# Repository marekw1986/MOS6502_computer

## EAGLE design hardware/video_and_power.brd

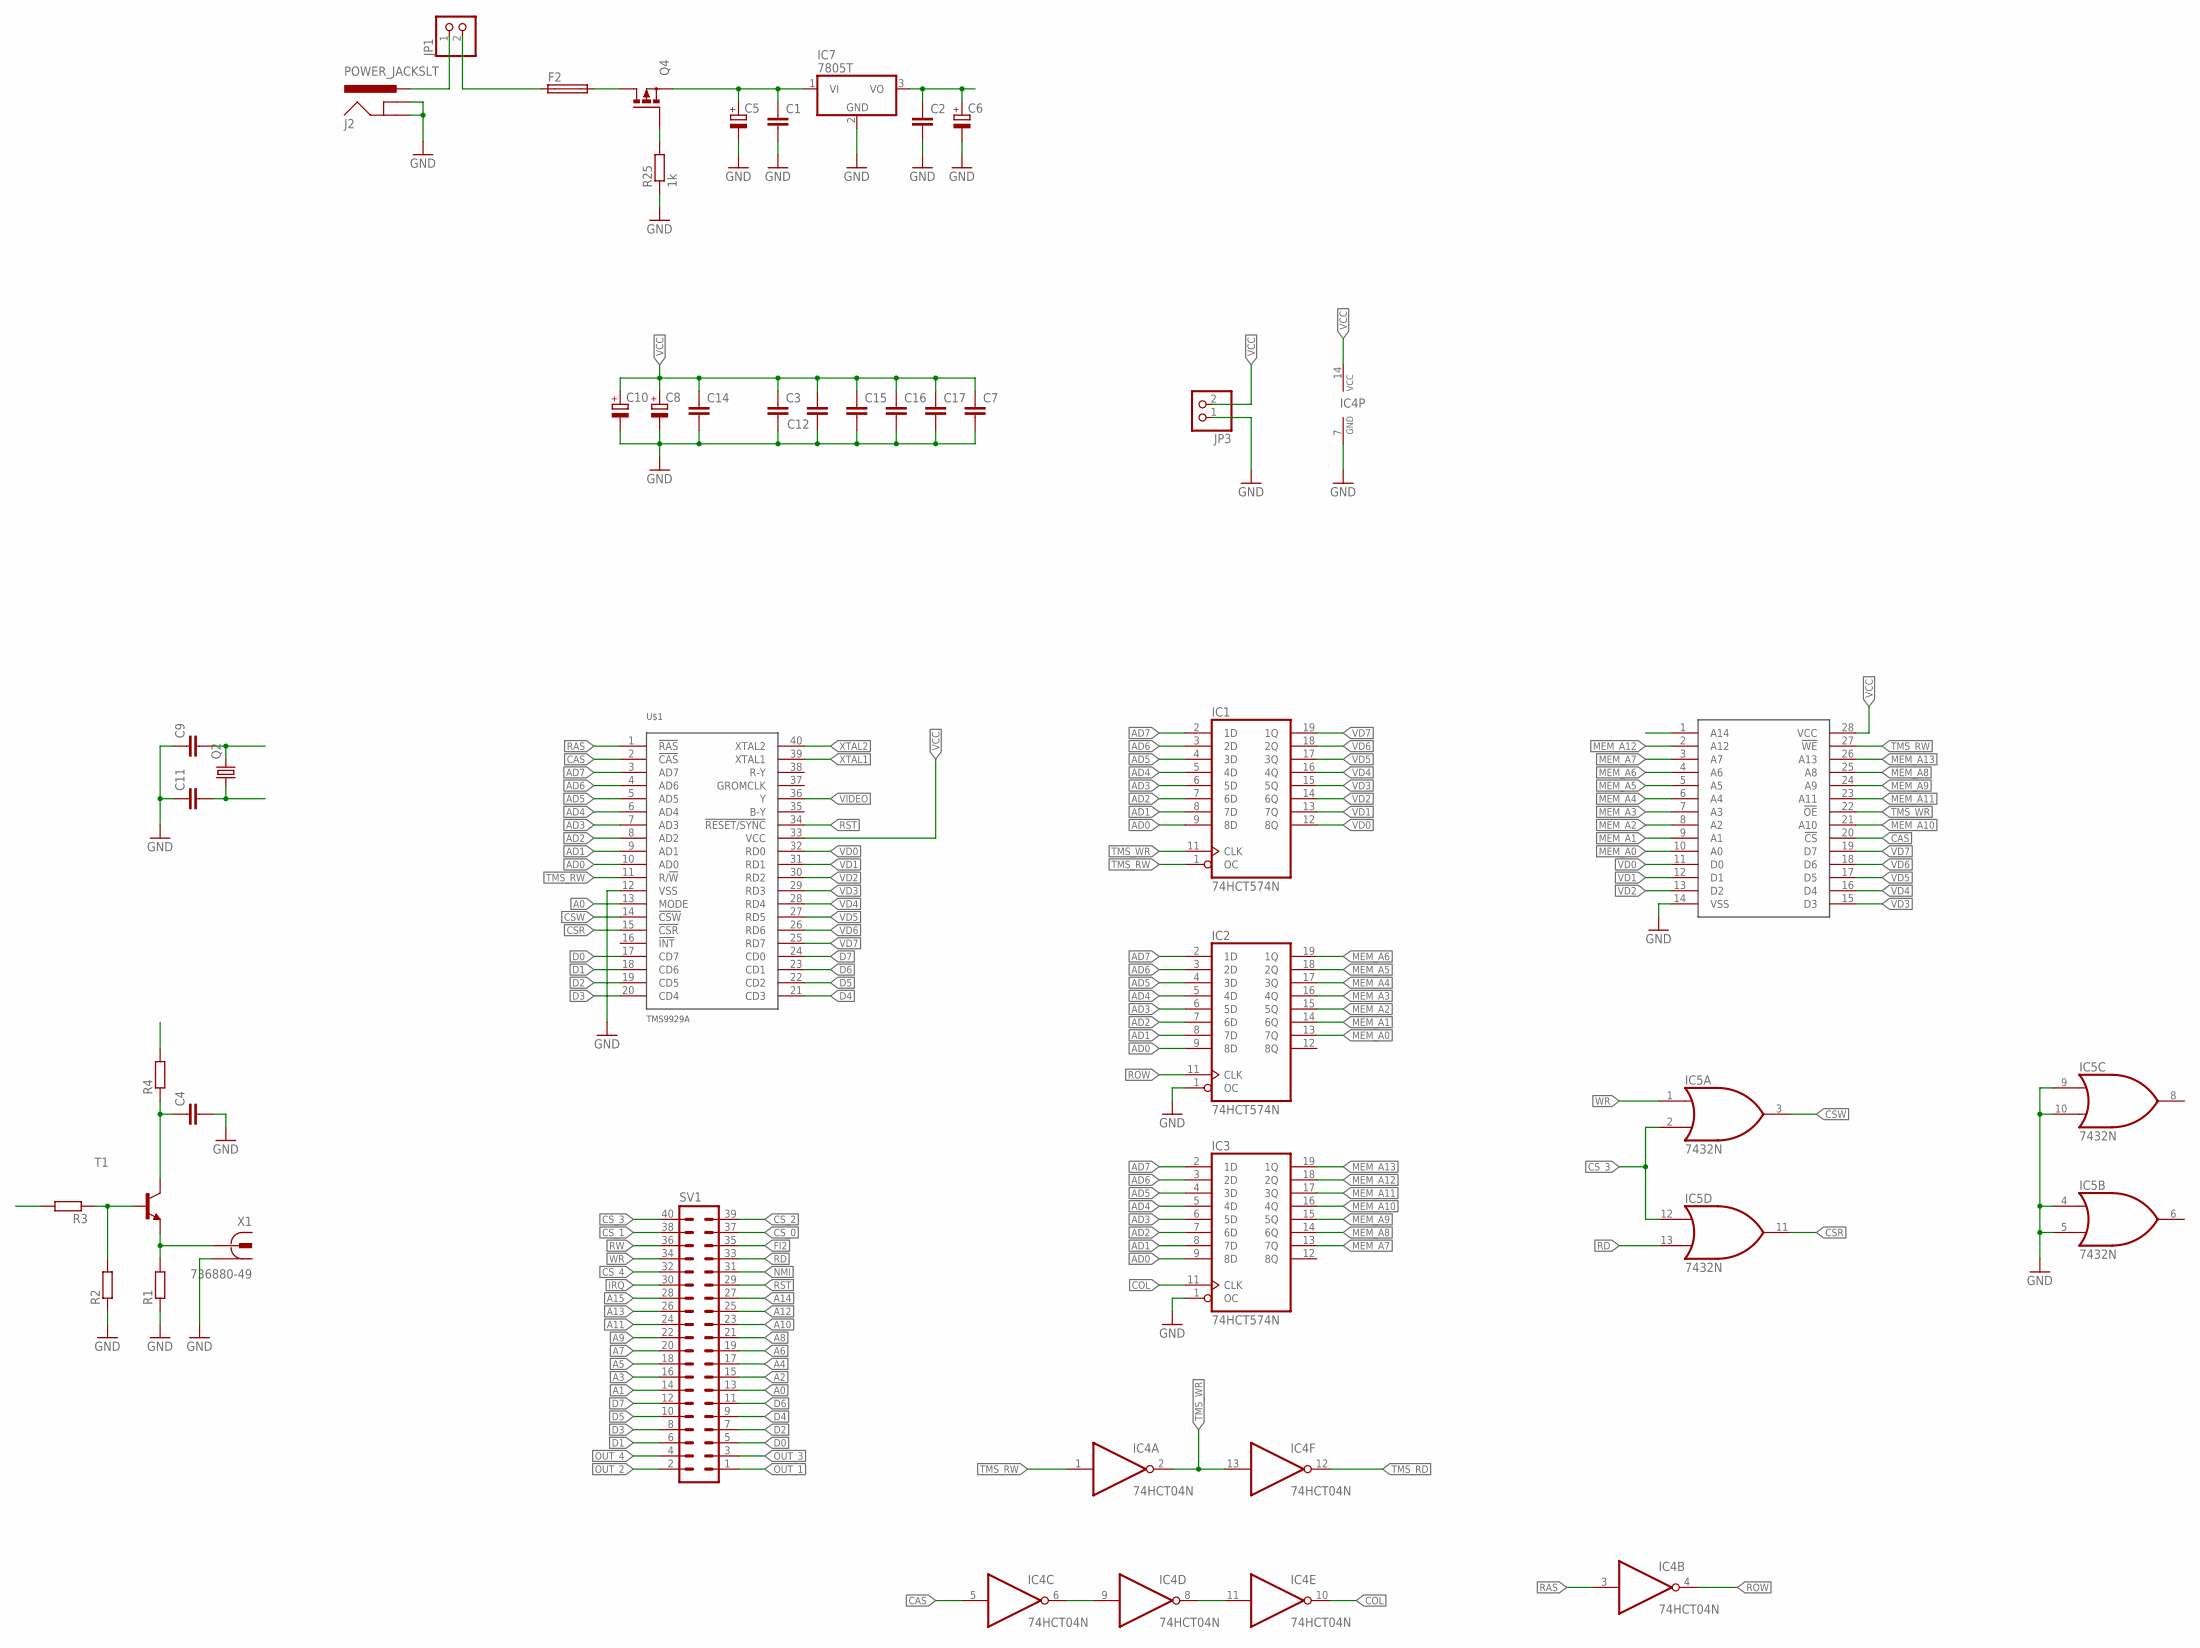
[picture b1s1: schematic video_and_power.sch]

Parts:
C1, C2, C7, C14, C15: C-EUC1206; C1206
C3, C4, C9, C11, C12, C16, C17: C-EUC0603; C0603
C5, C6, C8, C10: CPOL-EUE5-10.5; E5-10,5
F2: SH22,5; MPN 0031.8201
IC1, IC2, IC3: 74HCT574N; DIL20
IC4: 74HCT04N; DIL14
IC5: 7432N; DIL14
IC7: 7805T; TO220H
J2: POWER_JACKSLT; POWER_JACK_SLOT
JP1: PINHD-1X2; 1X02
JP3: PINHD-1X2/90; 1X02/90
Q2: CRYSTALHC49S; HC49/S
Q4: P-MOSFET-SO8; SO-08
R1, R2: R-EU_R0603; R0603
R3: R-EU_0204/7; 0204/7
R4: R-EU_R0805; R0805
R25: 1k; R0603
SV1: ML40L
T1: 2N4401-NPN-TO92-EBC; TO92-EBC
U$1: TMS9929A; DIL40
U$2: 62256; DIL28-6
X1: 736880-49

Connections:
9V: C1.1, C5.+, IC7.1 (VI), Q4.1 (S), Q4.2 (S), Q4.3 (S)
A0: SV1.13, U$1.13 (MODE)
A1: SV1.14
A2: SV1.15
A3: SV1.16
A4: SV1.17
A5: SV1.18
A6: SV1.19
A7: SV1.20
A8: SV1.21
A9: SV1.22
A10: SV1.23
A11: SV1.24
A12: SV1.25
A13: SV1.26
A14: SV1.27
A15: SV1.28
AD0: IC1.9 (8D), IC2.9 (8D), IC3.9 (8D), U$1.10 (AD0)
AD1: IC1.8 (7D), IC2.8 (7D), IC3.8 (7D), U$1.9 (AD1)
AD2: IC1.7 (6D), IC2.7 (6D), IC3.7 (6D), U$1.8 (AD2)
AD3: IC1.6 (5D), IC2.6 (5D), IC3.6 (5D), U$1.7 (AD3)
AD4: IC1.5 (4D), IC2.5 (4D), IC3.5 (4D), U$1.6 (AD4)
AD5: IC1.4 (3D), IC2.4 (3D), IC3.4 (3D), U$1.5 (AD5)
AD6: IC1.3 (2D), IC2.3 (2D), IC3.3 (2D), U$1.4 (AD6)
AD7: IC1.2 (1D), IC2.2 (1D), IC3.2 (1D), U$1.3 (AD7)
CAS: IC4.5 (I), U$1.2 (!CAS), U$2.20 (!CS)
COL: IC3.11 (CLK), IC4.10 (O)
CSR: IC5.11 (O), U$1.15 (!CSR)
CSW: IC5.3 (O), U$1.14 (!CSW)
CS_0: SV1.37
CS_1: SV1.38
CS_2: SV1.39
CS_3: IC5.2 (I1), IC5.12 (I0), SV1.40
CS_4: SV1.32
D0: SV1.5, U$1.17 (CD7)
D1: SV1.6, U$1.18 (CD6)
D2: SV1.7, U$1.19 (CD5)
D3: SV1.8, U$1.20 (CD4)
D4: SV1.9, U$1.21 (CD3)
D5: SV1.10, U$1.22 (CD2)
D6: SV1.11, U$1.23 (CD1)
D7: SV1.12, U$1.24 (CD0)
FI2: SV1.35
GND: C1.2, C2.2, C3.2, C4.2, C5.-, C6.-, C7.2, C8.-, C9.1, C10.-, C11.1, C12.1, C14.2, C15.2, C16.2, C17.2, IC1.10 (GND), IC2.1 (OC), IC2.10 (GND), IC3.1 (OC), IC3.10 (GND), IC4.7 (GND), IC5.4 (I0), IC5.5 (I1), IC5.7 (GND), IC5.9 (I0), IC5.10 (I1), IC7.2 (GND), J2.GND@1 (GNDBREAK), J2.GND@2 (GND), JP3.1, R1.1, R2.1, R25.1, U$1.12 (VSS), U$2.14 (VSS), X1.1, X1.1@1 (1), X1.1@2 (1)
IRQ: SV1.30
MEM_A0: IC2.13 (7Q), U$2.10 (A0)
MEM_A1: IC2.14 (6Q), U$2.9 (A1)
MEM_A2: IC2.15 (5Q), U$2.8 (A2)
MEM_A3: IC2.16 (4Q), U$2.7 (A3)
MEM_A4: IC2.17 (3Q), U$2.6 (A4)
MEM_A5: IC2.18 (2Q), U$2.5 (A5)
MEM_A6: IC2.19 (1Q), U$2.4 (A6)
MEM_A7: IC3.13 (7Q), U$2.3 (A7)
MEM_A8: IC3.14 (6Q), U$2.25 (A8)
MEM_A9: IC3.15 (5Q), U$2.24 (A9)
MEM_A10: IC3.16 (4Q), U$2.21 (A10)
MEM_A11: IC3.17 (3Q), U$2.23 (A11)
MEM_A12: IC3.18 (2Q), U$2.2 (A12)
MEM_A13: IC3.19 (1Q), U$2.26 (A13)
unnamed: IC4.6 (O), IC4.9 (I)
unnamed: IC4.8 (O), IC4.11 (I)
unnamed: Q4.4 (G), R25.2
unnamed: J2.PWR, JP1.1
unnamed: R1.2, T1.E, X1.2
unnamed: R2.2, R3.1, T1.B
unnamed: C4.1, R4.1, T1.C
unnamed: F2.1, JP1.2
unnamed: F2.2, Q4.5 (D), Q4.6 (D), Q4.7 (D), Q4.8 (D)
NMI: SV1.31
OUT_1: SV1.1
OUT_2: SV1.2
OUT_3: SV1.3, U$2.1 (A14)
OUT_4: SV1.4
RAS: IC4.3 (I), U$1.1 (!RAS)
RD: IC5.13 (I1), SV1.33
ROW: IC2.11 (CLK), IC4.4 (O)
RST: SV1.29, U$1.34 (!RESET/SYNC)
RW: SV1.36
TMS_RD: IC4.12 (O)
TMS_RW: IC1.1 (OC), IC4.1 (I), U$1.11 (R/!W), U$2.27 (!WE)
TMS_WR: IC1.11 (CLK), IC4.2 (O), IC4.13 (I), U$2.22 (!OE)
VCC: C2.1, C3.1, C6.+, C7.1, C8.+, C10.+, C12.2, C14.1, C15.1, C16.1, C17.1, IC1.20 (VCC), IC2.20 (VCC), IC3.20 (VCC), IC4.14 (VCC), IC5.14 (VCC), IC7.3 (VO), JP3.2, R4.2, U$1.33 (VCC), U$2.28 (VCC)
VD0: IC1.12 (8Q), U$1.32 (RD0), U$2.11 (D0)
VD1: IC1.13 (7Q), U$1.31 (RD1), U$2.12 (D1)
VD2: IC1.14 (6Q), U$1.30 (RD2), U$2.13 (D2)
VD3: IC1.15 (5Q), U$1.29 (RD3), U$2.15 (D3)
VD4: IC1.16 (4Q), U$1.28 (RD4), U$2.16 (D4)
VD5: IC1.17 (3Q), U$1.27 (RD5), U$2.17 (D5)
VD6: IC1.18 (2Q), U$1.26 (RD6), U$2.18 (D6)
VD7: IC1.19 (1Q), U$1.25 (RD7), U$2.19 (D7)
VIDEO: R3.2, U$1.36 (Y)
WR: IC5.1 (I0), SV1.34
XTAL1: C9.2, Q2.2, U$1.39 (XTAL1)
XTAL2: C11.2, Q2.1, U$1.40 (XTAL2)

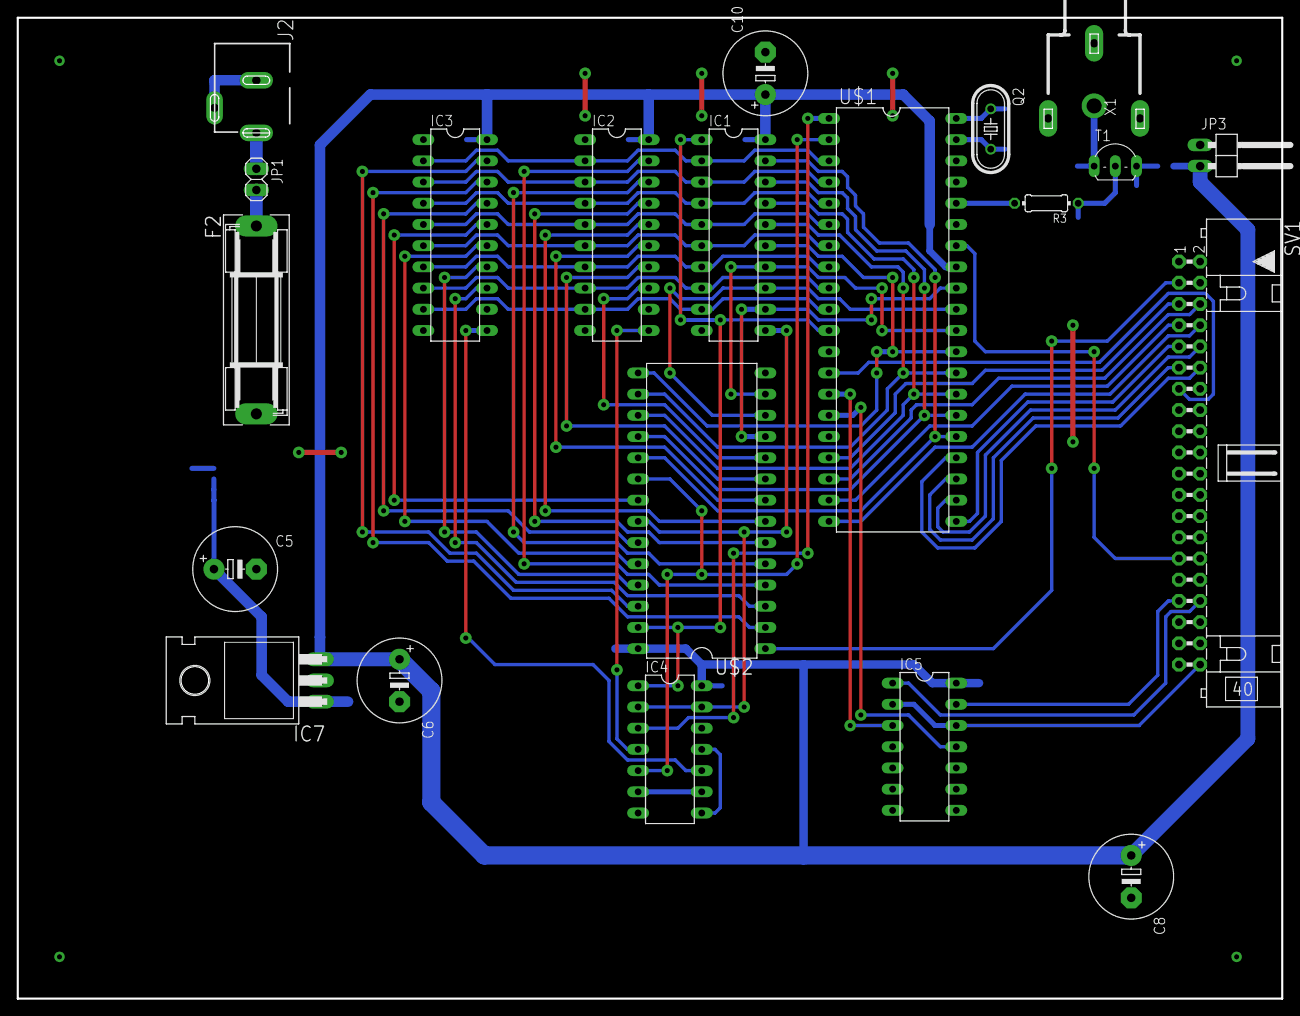
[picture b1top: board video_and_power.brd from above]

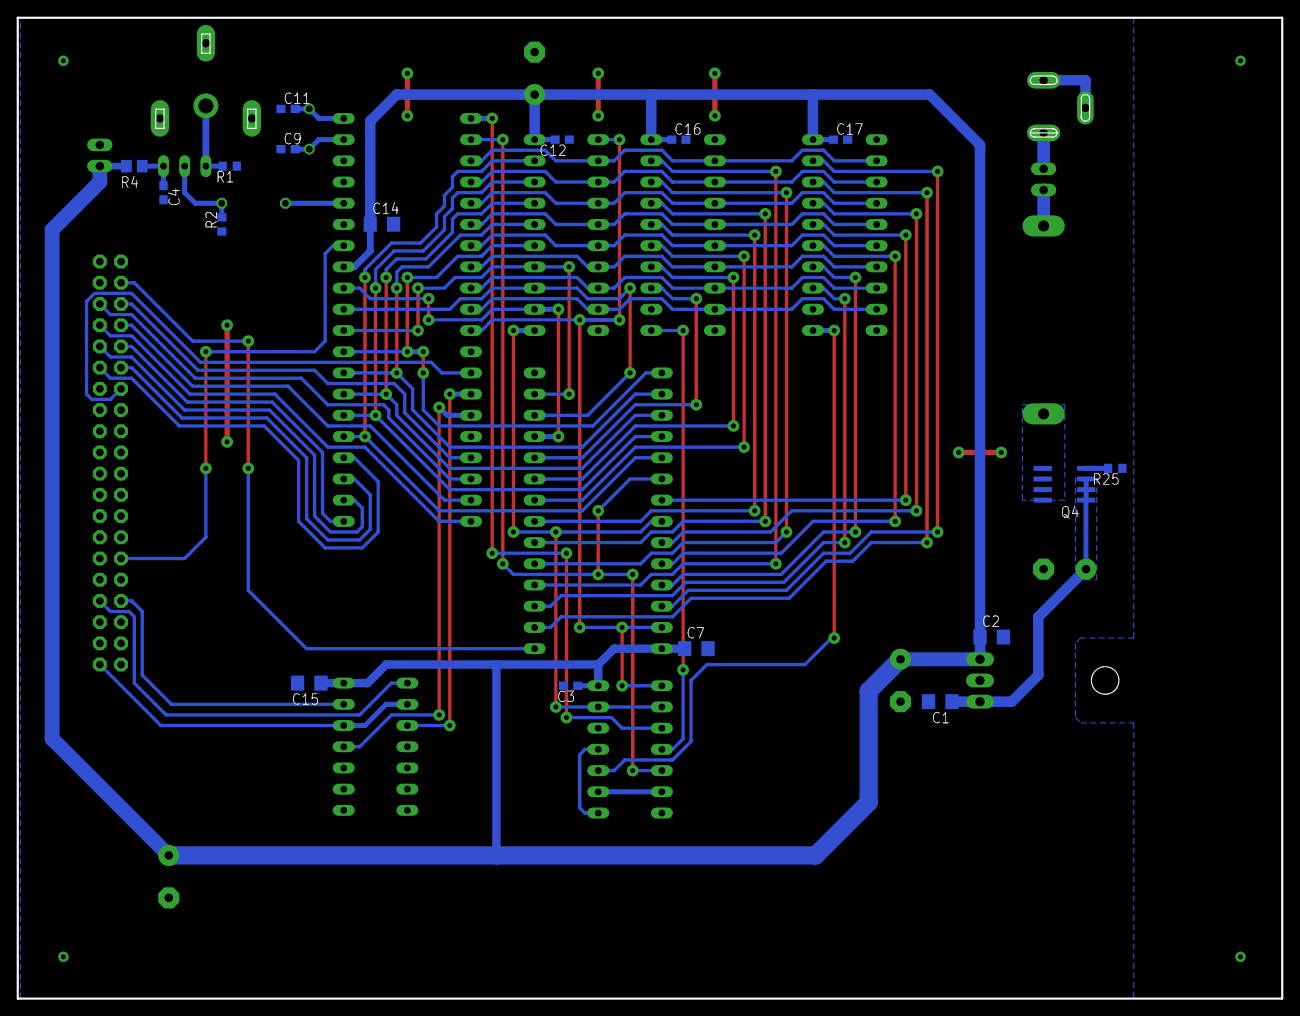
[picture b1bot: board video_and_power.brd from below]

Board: 2 copper layers, 151.4 x 117.5 mm, 38 parts (17 on the bottom side), 67 nets.

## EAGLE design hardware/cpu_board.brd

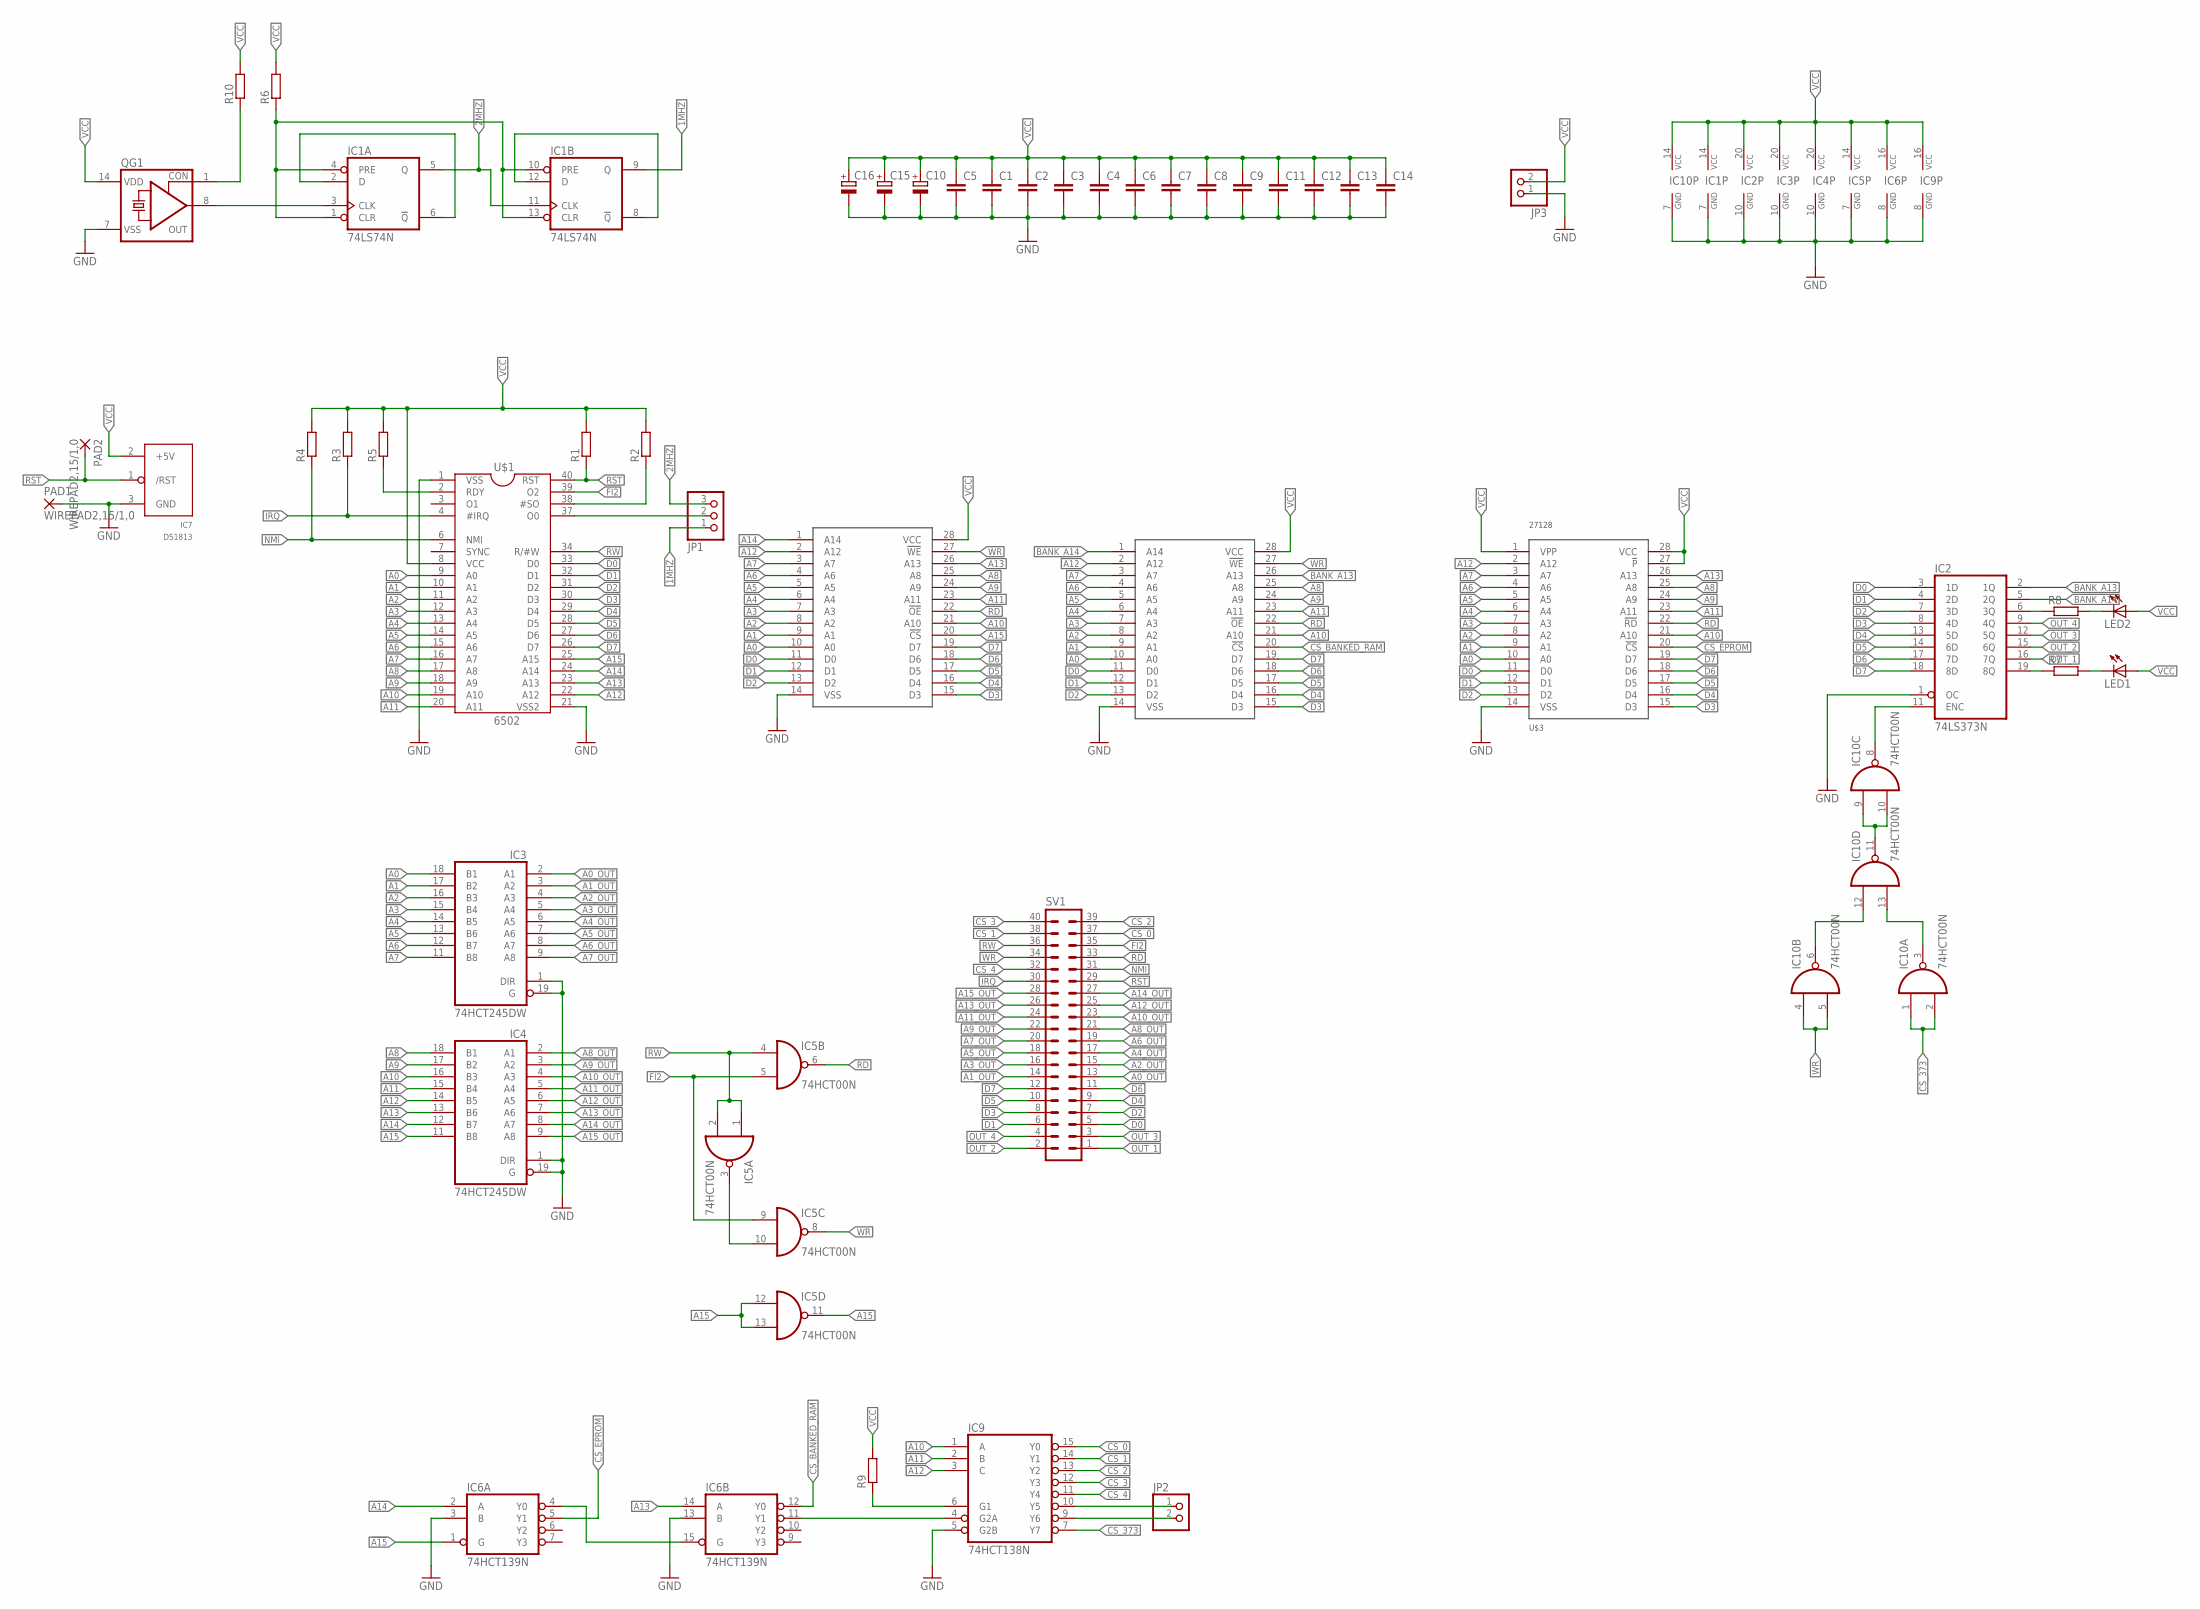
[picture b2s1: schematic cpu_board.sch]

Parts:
C1, C2, C3, C4, C6, C8, C9: C-EUC1206; C1206
C5, C7, C14: C-EUC0603; C0603
C10: CPOL-EUE5-10.5; E5-10,5
C11, C12, C13: C-EUC0805; C0805
C15, C16: CPOL-EUSMCB; SMC_B
IC1: 74LS74N; DIL14
IC2: 74LS373N; DIL20
IC3, IC4: 74HCT245DW; SO20W
IC5, IC10: 74HCT00N; DIL14
IC6: 74HCT139N; DIL16
IC7: DS1813; TO-92
IC9: 74HCT138N; DIL16
JP1: PINHD-1X3; 1X03
JP2, JP3: PINHD-1X2/90; 1X02/90
LED1, LED2: LED5MM
PAD1, PAD2: WIREPAD2,15/1,0; 2,15/1,0
QG1: CRYSTAL_RES-SG51; SG51
R1, R2, R3, R4, R5, R7, R8, R10: R-EU_R1206; R1206
R6: R-EU_M1206; M1206
R9: R-EU_0204/7; 0204/7
SV1: ML40L
U$1: 6502; DIL40
U$2, U$4: 62256; DIL28-6
U$3: 27128; DIL28

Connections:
1MHZ: IC1.9 (Q), JP1.1
2MHZ: IC1.5 (Q), IC1.11 (CLK), JP1.3
!A15: IC5.11 (O), IC6.1 (G)
A0: IC3.18 (B1), U$1.9 (A0), U$2.10 (A0), U$3.10 (A0), U$4.10 (A0)
A0_OUT: IC3.2 (A1), SV1.13
A1: IC3.17 (B2), U$1.10 (A1), U$2.9 (A1), U$3.9 (A1), U$4.9 (A1)
A1_OUT: IC3.3 (A2), SV1.14
A2: IC3.16 (B3), U$1.11 (A2), U$2.8 (A2), U$3.8 (A2), U$4.8 (A2)
A2_OUT: IC3.4 (A3), SV1.15
A3: IC3.15 (B4), U$1.12 (A3), U$2.7 (A3), U$3.7 (A3), U$4.7 (A3)
A3_OUT: IC3.5 (A4), SV1.16
A4: IC3.14 (B5), U$1.13 (A4), U$2.6 (A4), U$3.6 (A4), U$4.6 (A4)
A4_OUT: IC3.6 (A5), SV1.17
A5: IC3.13 (B6), U$1.14 (A5), U$2.5 (A5), U$3.5 (A5), U$4.5 (A5)
A5_OUT: IC3.7 (A6), SV1.18
A6: IC3.12 (B7), U$1.15 (A6), U$2.4 (A6), U$3.4 (A6), U$4.4 (A6)
A6_OUT: IC3.8 (A7), SV1.19
A7: IC3.11 (B8), U$1.16 (A7), U$2.3 (A7), U$3.3 (A7), U$4.3 (A7)
A7_OUT: IC3.9 (A8), SV1.20
A8: IC4.18 (B1), U$1.17 (A8), U$2.25 (A8), U$3.25 (A8), U$4.25 (A8)
A8_OUT: IC4.2 (A1), SV1.21
A9: IC4.17 (B2), U$1.18 (A9), U$2.24 (A9), U$3.24 (A9), U$4.24 (A9)
A9_OUT: IC4.3 (A2), SV1.22
A10: IC4.16 (B3), IC9.1 (A), U$1.19 (A10), U$2.21 (A10), U$3.21 (A10), U$4.21 (A10)
A10_OUT: IC4.4 (A3), SV1.23
A11: IC4.15 (B4), IC9.2 (B), U$1.20 (A11), U$2.23 (A11), U$3.23 (A11), U$4.23 (A11)
A11_OUT: IC4.5 (A4), SV1.24
A12: IC4.14 (B5), IC9.3 (C), U$1.22 (A12), U$2.2 (A12), U$3.2 (A12), U$4.2 (A12)
A12_OUT: IC4.6 (A5), SV1.25
A13: IC4.13 (B6), IC6.14 (A), U$1.23 (A13), U$3.26 (A13), U$4.26 (A13)
A13_OUT: IC4.7 (A6), SV1.26
A14: IC4.12 (B7), IC6.2 (A), U$1.24 (A14), U$4.1 (A14)
A14_OUT: IC4.8 (A7), SV1.27
A15: IC4.11 (B8), IC5.12 (I0), IC5.13 (I1), U$1.25 (A15), U$4.20 (!CS)
A15_OUT: IC4.9 (A8), SV1.28
BANK_A13: IC2.2 (1Q), U$2.26 (A13)
BANK_A14: IC2.5 (2Q), U$2.1 (A14)
CS_0: IC9.15 (Y0), SV1.37
CS_1: IC9.14 (Y1), SV1.38
CS_2: IC9.13 (Y2), SV1.39
CS_3: IC9.12 (Y3), SV1.40
CS_4: IC9.11 (Y4), SV1.32
CS_373: IC9.7 (Y7), IC10.1 (I0), IC10.2 (I1)
CS_BANKED_RAM: IC6.12 (Y0), U$2.20 (!CS)
CS_EPROM: IC6.5 (Y1), U$3.20 (!CS)
D0: IC2.3 (1D), SV1.5, U$1.33 (D0), U$2.11 (D0), U$3.11 (D0), U$4.11 (D0)
D1: IC2.4 (2D), SV1.6, U$1.32 (D1), U$2.12 (D1), U$3.12 (D1), U$4.12 (D1)
D2: IC2.7 (3D), SV1.7, U$1.31 (D2), U$2.13 (D2), U$3.13 (D2), U$4.13 (D2)
D3: IC2.8 (4D), SV1.8, U$1.30 (D3), U$2.15 (D3), U$3.15 (D3), U$4.15 (D3)
D4: IC2.13 (5D), SV1.9, U$1.29 (D4), U$2.16 (D4), U$3.16 (D4), U$4.16 (D4)
D5: IC2.14 (6D), SV1.10, U$1.28 (D5), U$2.17 (D5), U$3.17 (D5), U$4.17 (D5)
D6: IC2.17 (7D), SV1.11, U$1.27 (D6), U$2.18 (D6), U$3.18 (D6), U$4.18 (D6)
D7: IC2.18 (8D), SV1.12, U$1.26 (D7), U$2.19 (D7), U$3.19 (D7), U$4.19 (D7)
FI2: IC5.5 (I1), IC5.9 (I0), SV1.35, U$1.39 (O2)
GND: C1.2, C2.2, C3.2, C4.2, C5.2, C6.2, C7.2, C8.2, C9.2, C10.-, C11.2, C12.2, C13.2, C14.2, C15.-, C16.-, IC1.7 (GND), IC2.1 (OC), IC2.10 (GND), IC3.1 (DIR), IC3.10 (GND), IC3.19 (G), IC4.1 (DIR), IC4.10 (GND), IC4.19 (G), IC5.7 (GND), IC6.3 (B), IC6.8 (GND), IC6.13 (B), IC7.3 (GND), IC9.5 (G2B), IC9.8 (GND), IC10.7 (GND), JP3.1, PAD1.1, QG1.7 (VSS), U$1.1 (VSS), U$1.21 (VSS2), U$2.14 (VSS), U$3.14 (VSS), U$4.14 (VSS)
IRQ: R3.1, SV1.30, U$1.4 (#IRQ)
unnamed: IC1.1 (CLR), IC1.4 (PRE), IC1.10 (PRE), IC1.13 (CLR), R6.1
unnamed: R2.1, U$1.38 (#SO)
unnamed: IC2.19 (8Q), R7.1
unnamed: LED1.K (C), R7.2
unnamed: R5.1, U$1.2 (RDY)
unnamed: JP1.2, U$1.37 (O0)
unnamed: QG1.1 (CON), R10.1
unnamed: IC1.3 (CLK), QG1.8 (OUT)
unnamed: IC1.2 (D), IC1.6 (!Q)
unnamed: IC1.8 (!Q), IC1.12 (D)
unnamed: IC2.11 (ENC), IC10.8 (O)
unnamed: IC10.9 (I0), IC10.10 (I1), IC10.11 (O)
unnamed: IC10.3 (O), IC10.13 (I1)
unnamed: IC10.6 (O), IC10.12 (I0)
unnamed: IC2.6 (3Q), R8.1
unnamed: IC9.10 (Y5), JP2.1
unnamed: LED2.K (C), R8.2
unnamed: IC5.3 (O), IC5.10 (I1)
unnamed: IC6.4 (Y0), IC6.15 (G)
unnamed: IC9.6 (G1), R9.1
unnamed: IC6.11 (Y1), IC9.4 (G2A)
unnamed: IC9.9 (Y6), JP2.2
NMI: R4.1, SV1.31, U$1.6 (NMI)
OUT_1: IC2.16 (7Q), SV1.1
OUT_2: IC2.15 (6Q), SV1.2
OUT_3: IC2.12 (5Q), SV1.3
OUT_4: IC2.9 (4Q), SV1.4
RD: IC5.6 (O), SV1.33, U$2.22 (!OE), U$3.22 (!RD), U$4.22 (!OE)
RST: IC7.1 (/RST), PAD2.1, R1.1, SV1.29, U$1.40 (RST)
RW: IC5.1 (I0), IC5.2 (I1), IC5.4 (I0), SV1.36, U$1.34 (R/#W)
VCC: C1.1, C2.1, C3.1, C4.1, C5.1, C6.1, C7.1, C8.1, C9.1, C10.+, C11.1, C12.1, C13.1, C14.1, C15.+, C16.+, IC1.14 (VCC), IC2.20 (VCC), IC3.20 (VCC), IC4.20 (VCC), IC5.14 (VCC), IC6.16 (VCC), IC7.2 (+5V), IC9.16 (VCC), IC10.14 (VCC), JP3.2, LED1.A, LED2.A, QG1.14 (VDD), R1.2, R2.2, R3.2, R4.2, R5.2, R6.2, R9.2, R10.2, U$1.8 (VCC), U$2.28 (VCC), U$3.1 (VPP), U$3.27 (!P), U$3.28 (VCC), U$4.28 (VCC)
WR: IC5.8 (O), IC10.4 (I0), IC10.5 (I1), SV1.34, U$2.27 (!WE), U$4.27 (!WE)

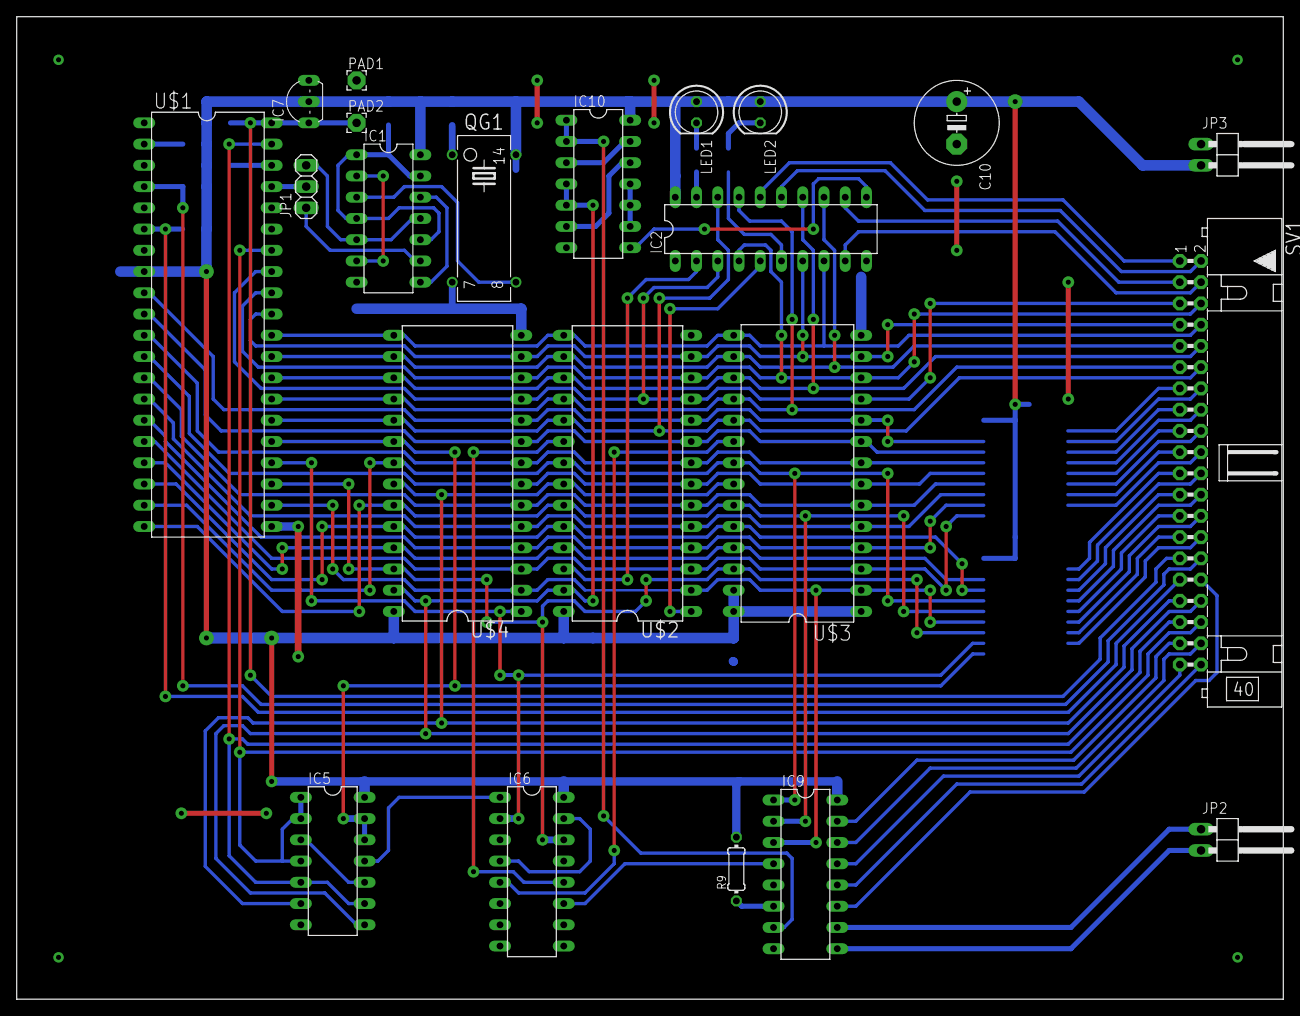
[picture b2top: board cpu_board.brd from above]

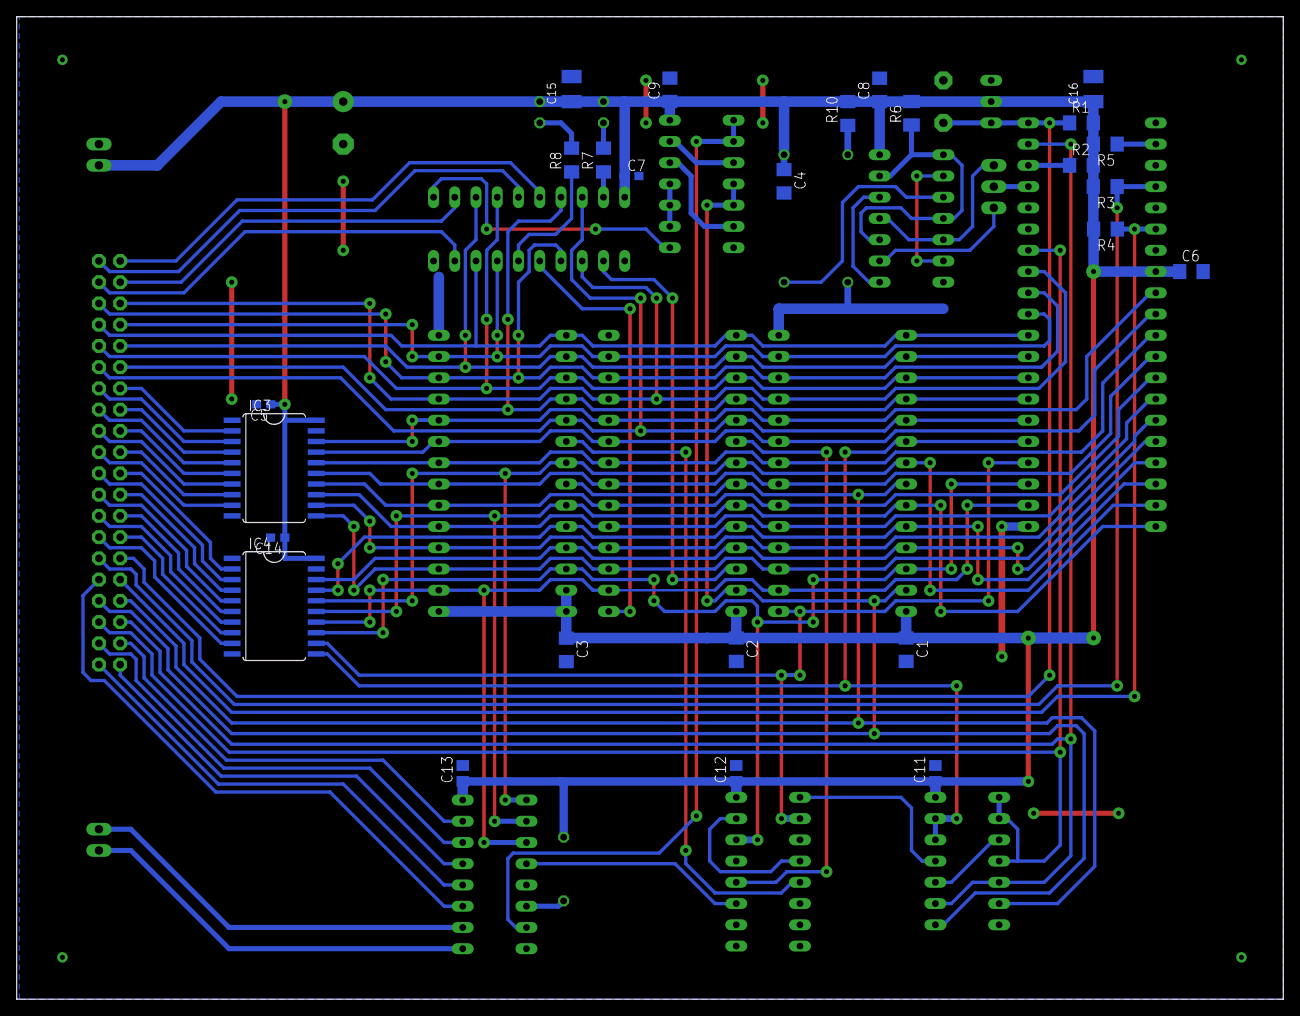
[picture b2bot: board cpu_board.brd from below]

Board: 2 copper layers, 151.4 x 117.5 mm, 48 parts (26 on the bottom side), 88 nets.

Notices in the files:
parts and their libraries:
SparkFun-Connectors: Licensing: Creative Commons ShareAlike 4.0 International - https://creativecommons.org/licenses/by-sa/4.0
